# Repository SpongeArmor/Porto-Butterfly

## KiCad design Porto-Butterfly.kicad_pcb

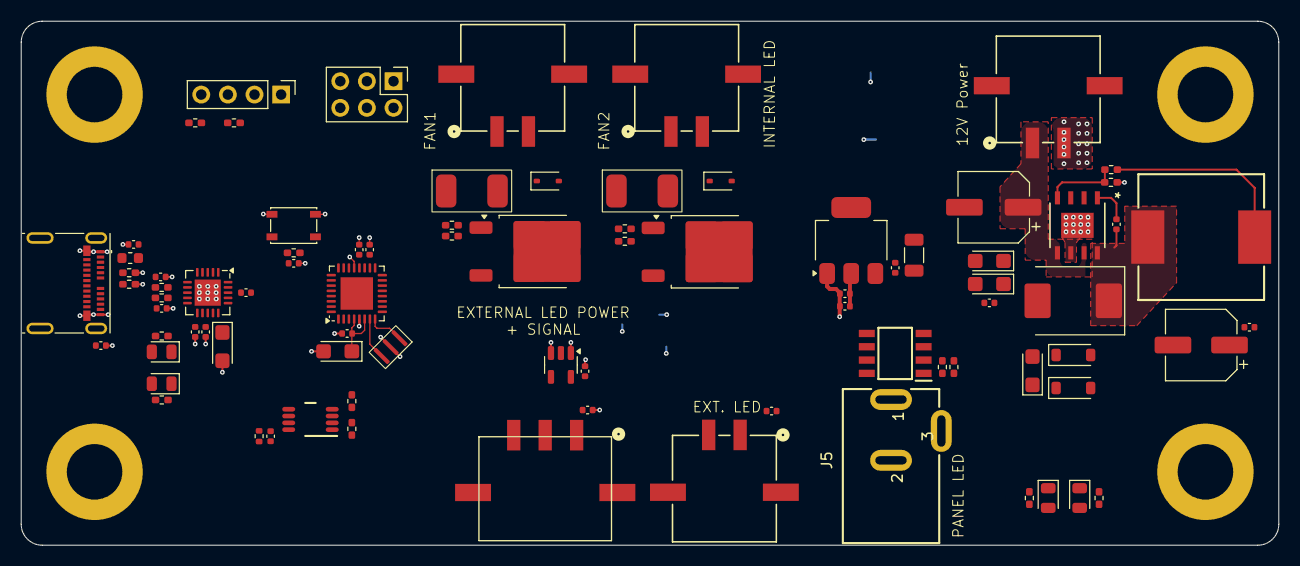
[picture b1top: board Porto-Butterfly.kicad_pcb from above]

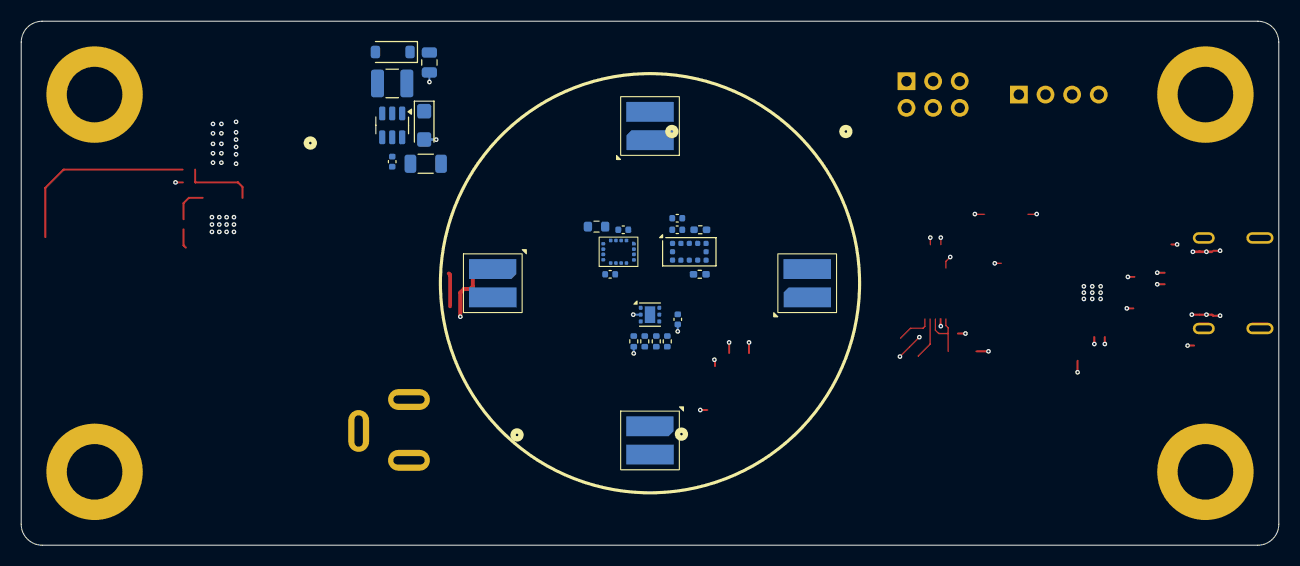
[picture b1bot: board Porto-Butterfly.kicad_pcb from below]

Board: 4 copper layers, 120.0 x 50.0 mm, 114 parts (26 on the bottom side), 65 nets.

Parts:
C1, C2, C5, C12, C15, C16, C18, C19, C20, C21, C22, C23, C24, C28, C31, C33, C35, C37: 100nF; C_0402_1005Metric
C3, C4: 47pF; C_0402_1005Metric
C6, C30: 1uF; CP_EIA-3216-10_Kemet-I
C7, C11, C36, C39: 4.7uF; CP_EIA-3216-10_Kemet-I
C10: 100uF; CP_Elec_6.3x5.4
C13, C25, C26, C29: 10nF; C_0402_1005Metric
C17: 4.7uF; C_0402_1005Metric
C27: 330uF; CP_Elec_6.3x7.7
C32: 22uF; C_1206_3216Metric
C34: 10uF; C_0402_1005Metric
C38: 1uF; C_0805_2012Metric
C40: 220nF; C_0402_1005Metric
D1, D5, D9: Green; LED_0805_2012Metric
D2, D6: B5819WS; D_SOD-323
D3: B540C; D_SMC
D4: Yellow; LED_0805_2012Metric
D7, D8: MBR0520LT; D_SOD-123
D10: MBR0530; D_SOD-123
D11, D12, D13, D14: LED; GW Q9LR33
F1, F2: 0451010.MRL
FB1: 150Ω@100MHz; L_0603_1608Metric
H1, H2, H3, H4: MountingHole_Pad; MountingHole_5.3mm_M5_DIN965_Pad
J1: 1054500101; USB_C_Receptacle_Molex_105450-0101
J2: AVR-ISP-6; PinHeader_2x03_P2.54mm_Vertical
J3, J9, J10, J11: 436500212
J4: Conn_01x04; PinHeader_1x04_P2.54mm_Vertical
J5: 694106301002
J8: 436500312
L1: 10uH; L_1210_3225Metric
L2: 15uH; INDPM120120X800N
Q1: FDS8949; SOIC127P600X175-8N
Q4, Q5: NCE3080KA; TO-252-2
R1, R2: 22; R_0402_1005Metric_Pad0.72x0.64mm_HandSolder
R3, R22: 4.7k; R_0402_1005Metric_Pad0.72x0.64mm_HandSolder
R4, R9, R28, R29: 10k; R_0402_1005Metric_Pad0.72x0.64mm_HandSolder
R5, R6, R31, R32: 2.2k; R_0402_1005Metric_Pad0.72x0.64mm_HandSolder
R7, R11, R25: 100k; R_0402_1005Metric_Pad0.72x0.64mm_HandSolder
R10: 3.16k; R_0402_1005Metric_Pad0.72x0.64mm_HandSolder
R12, R23, R24: 100; R_0402_1005Metric_Pad0.72x0.64mm_HandSolder
R13: 0.6; R_1206_3216Metric
R15, R27: 1k; R_0402_1005Metric_Pad0.72x0.64mm_HandSolder
R16, R26: 5.1k; R_0402_1005Metric_Pad0.72x0.64mm_HandSolder
R30: 200k; R_0402_1005Metric
R33, R34, R35, R36: 0; R_0402_1005Metric
R37: 3.3M; R_0603_1608Metric
SW1: RESET; SW_SPST_PTS810
U1: ATmega328P-M; QFN-32-1EP_5x5mm_P0.5mm_EP3.1x3.1mm
U2: FT231XQ; QFN-20-1EP_4x4mm_P0.5mm_EP2.5x2.5mm
U4: SN74LVC1G125DBV; SOT-23-5
U5: TPS5450DDAR; DDA8_3P1X2P4-L
U7: AMS1117-3.3; SOT-223-3_TabPin2
U8: VL53L0CXV0DH; ST_VL53L1x
U9: LSF0102DCTR; DCT0008A_M
U10: TMP117AIDRVR; WSON-6-1EP_2x2mm_P0.65mm_EP1x1.6mm
U11: AS7331
U13: TPS61165DBV; SOT-23-6
Y1: 16MHz; SMD3213-3P

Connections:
+3.3V: C17.1, C18.2, C24.1, C34.1, C35.1, C37.1, D9.2 (A), J4.2, R5.1, R6.1, R31.1, R32.1, U7.2 (VO), U8.1 (AVDDVCSEL), U8.11 (AVDD), U9.2 (V_{REFA}), U11.7 (VDDD), U11.14 (VDDA)
+5V: C2.1, C6.1, C20.1, C21.2, C22.1, C23.1, C30.1, C31.1, C32.1, C33.1, D7.1 (K), D8.1 (K), J2.2, J8.1, J11.1, R4.1, R28.1, R29.1, R30.1, R35.1, U1.4 (VCC), U1.6 (VCC), U1.18 (AVCC), U4.5 (VCC), U7.3 (VI), U10.5 (V+)
+5VA: C27.1, C28.1, C39.1, D4.2 (A), D8.2 (A), L1.1, L2.2, R9.1, U13.1 (VIN)
+12V: F1.1, F2.1, J5.1
/Fan/FAN1_PWM: R23.1, U1.13 (PB1)
/Fan/FAN2_PWM: R24.1, U1.14 (PB2)
/Lighting/DIN_5V: J8.2, U4.4
/Lighting/INTERNAL_LED_PWM: U1.10 (PD6), U13.2 (CTRL)
/Lighting/LED_EXT_DAT: U1.12 (PB0), U4.2
/Lighting/PANEL_LED_PWM: R12.1, U1.9 (PD5)
/MCU/3V3OUT: C5.2, U2.10 (3V3OUT), U2.11 (~RESET), U2.20 (VCCIO)
/MCU/MISO: J2.1, U1.16 (PB4)
/MCU/MOSI: J2.4, U1.15 (PB3)
/MCU/PD2: R28.2, U1.32 (PD2), U8.7 (GPIO1)
/MCU/RX_FT232: U1.31 (PD1), U2.1 (RXD)
/MCU/RX_LED: D1.1 (K), U2.7 (CBUS2)
/MCU/SCK: J2.3, U1.17 (PB5)
/MCU/SCL: J4.3, R5.2, R34.1, U1.28 (PC5), U9.6 (B1), U10.1 (SCL)
/MCU/SDA: J4.4, R6.2, R33.1, U1.27 (PC4), U9.5 (B2), U10.6 (SDA)
/MCU/TX_FT232: U1.30 (PD0), U2.17 (TXD)
/MCU/TX_LED: D5.1 (K), U2.14 (CBUS1)
/MCU/~RESET: C12.1, C16.2, J2.5, R4.2, SW1.1 (A), U1.29 (~RESET/PC6)
/Power Supply/12VIN: C10.1, C11.1, C25.2, C36.1, J3.1, U5.5 (ENA), U5.7 (VIN)
/Power Supply/VSENSE: R9.2, R10.1, U5.4 (V_{sense})
/Sensors/SCL_3V3: R31.2, U8.10 (SCL), U9.3 (A1), U11.4 (SCL)
/Sensors/SDA_3V3: R32.2, U8.9 (SDA), U9.4 (A2), U11.5 (SDA)
GND: C1.2, C2.2, C3.2, C4.2, C5.1, C6.2, C7.2, C10.2, C11.2, C12.2, C13.2, C15.1, C17.2, C18.1, C19.2, C20.2, C21.1, C22.2, C23.2, C24.2, C25.1, C27.2, C28.2, C29.2, C30.2, C31.2, C32.2, C33.2, C34.2, C35.2, C36.2, C37.2, C38.2, C39.2, C40.2, D3.2 (A), H1.1, H2.1, H3.1, H4.1, J1.A1 (GND), J1.A12 (GND), J1.B1 (GND), J1.B12 (GND), J2.6, J3.2, J4.1, J8.3, J11.2, Q1.1 (S), Q4.3 (S), Q5.3 (S), R7.2, R10.2, R11.2, R13.2, R15.2, R16.1, R25.2, R26.2, R27.2, R36.1, R37.2, SW1.2 (B), U1.3 (GND), U1.5 (GND), U1.21 (GND), U1.33 (GND), U2.3 (GND), U2.13 (GND), U2.21 (GND), U4.1, U4.3 (GND), U5.6 (GND), U5.9 (GND), U7.1 (GND), U8.2 (AVSSVCSEL), U8.3 (GND), U8.4 (GND), U8.6 (GND), U8.12 (GND), U9.1 (GND), U10.2 (GND), U11.1 (VSSA), U11.2 (VSSA), U11.3 (A0), U11.6 (VSSD), U11.10 (A1), U11.11 (VSSA), U11.12 (VSSA), U11.15 (VSSA), U11.16 (VSSA), U13.4 (GND), Y1.2
unnamed: C3.1, J1.A6 (D+), J1.B6 (D+), R2.1
unnamed: C4.1, J1.A7 (D-), J1.B7 (D-), R1.1
unnamed: D1.2 (A), R3.2
unnamed: D2.2 (A), J9.2, Q4.2 (D)
unnamed: D2.1 (K), F1.2, J9.1
unnamed: C26.2, D3.1 (K), L2.1, U5.8 (PH)
unnamed: D4.1 (K), R15.1
unnamed: D5.2 (A), R22.2
unnamed: D6.2 (A), J10.2, Q5.2 (D)
unnamed: D6.1 (K), F2.2, J10.1
unnamed: D9.1 (K), R27.1
unnamed: D10.2 (A), L1.2, U13.3 (SW)
unnamed: C38.1, D10.1 (K), D11.2 (A)
unnamed: D11.1 (K), D12.2 (A)
unnamed: D12.1 (K), D13.2 (A)
unnamed: D13.1 (K), D14.2 (A)
unnamed: D14.1 (K), R13.1, U13.6 (FB)
unnamed: FB1.1, J1.A4 (VBUS), J1.A9 (VBUS), J1.B4 (VBUS), J1.B9 (VBUS)
unnamed: J1.A5 (CC1), R16.2
unnamed: J1.B5 (CC2), R26.1
unnamed: C29.1, J1.S1 (SHIELD)
unnamed: J5.2, J5.3, Q1.7 (D), Q1.8 (D)
unnamed: Q1.2 (G), R11.1, R12.2
unnamed: Q4.1 (G), R7.1, R23.2
unnamed: Q5.1 (G), R24.2, R25.1
unnamed: C1.1, U1.20 (AREF)
unnamed: U1.7 (XTAL1/PB6), Y1.3
unnamed: U1.8 (XTAL2/PB7), Y1.1
unnamed: R1.2, U2.9 (USBDM)
unnamed: R2.2, U2.8 (USBDP)
unnamed: C16.1, U2.18 (~DTR)
unnamed: C26.1, U5.1 (BOOT)
unnamed: R29.2, U8.5 (XSHUT)
unnamed: C19.1, R30.2, U9.7 (V_{REFB}), U9.8 (EN)
unnamed: R33.2, R34.2, R35.2, R36.2, U10.4 (ADD0)
unnamed: R37.1, U11.13 (REXT)
unnamed: C40.1, U13.5 (COMP)
VBUS: C7.1, C13.1, C15.2, D7.2 (A), FB1.2, R3.1, R22.1, U2.12 (VCC)

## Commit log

2025-02-19 V1.0 - Completed BOM
2025-02-23 Completed V1.0 draft layout - pending review
2025-02-26 Work-in-progress: Layout
